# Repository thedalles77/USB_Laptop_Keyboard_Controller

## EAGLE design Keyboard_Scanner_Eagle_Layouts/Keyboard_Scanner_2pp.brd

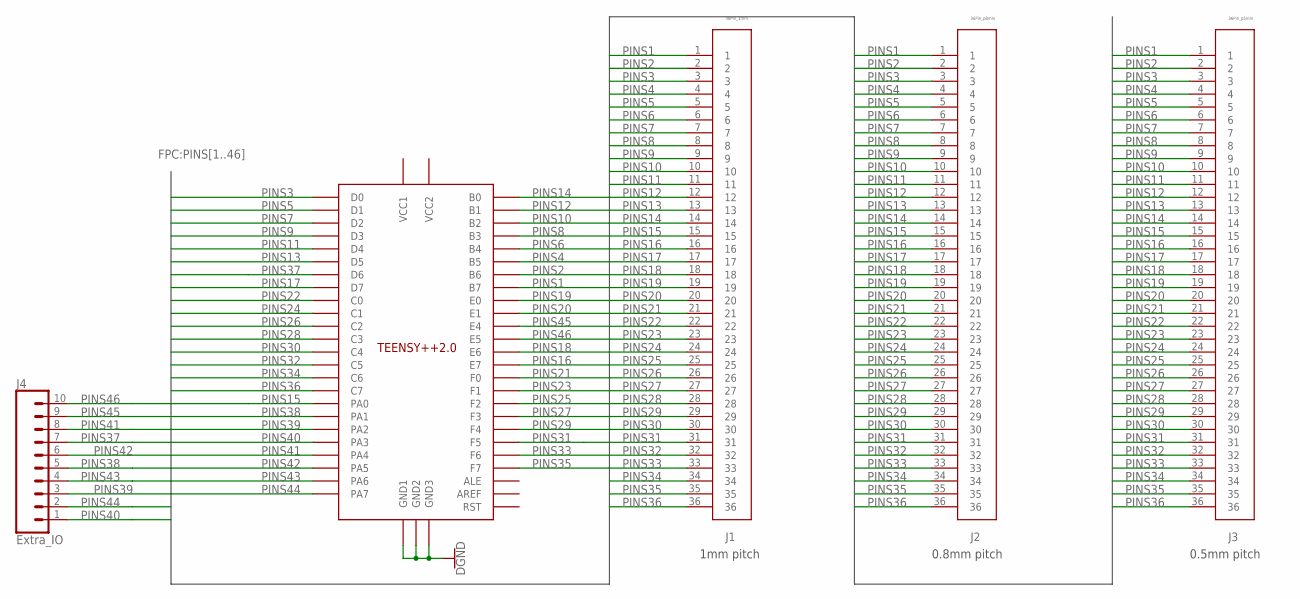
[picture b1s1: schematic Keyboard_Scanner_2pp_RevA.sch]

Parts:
J1: 36Pin_1mm; FPC36_1MM
J2: 36Pin_p8mm; FPC36_P8MM
J3: 36Pin_p5mm; FPC36_P5MM
J4: Extra_IO; 1X10
U$1: Teensy++2.0; TEENSYPP2.0

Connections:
GND: U$1.GND1, U$1.GND2, U$1.GND3
PINS1: J1.1, J2.1, J3.1, U$1.B7
PINS2: J1.2, J2.2, J3.2, U$1.B6
PINS3: J1.3, J2.3, J3.3, U$1.D0
PINS4: J1.4, J2.4, J3.4, U$1.B5
PINS5: J1.5, J2.5, J3.5, U$1.D1
PINS6: J1.6, J2.6, J3.6, U$1.B4
PINS7: J1.7, J2.7, J3.7, U$1.D2
PINS8: J1.8, J2.8, J3.8, U$1.B3
PINS9: J1.9, J2.9, J3.9, U$1.D3
PINS10: J1.10, J2.10, J3.10, U$1.B2
PINS11: J1.11, J2.11, J3.11, U$1.D4
PINS12: J1.12, J2.12, J3.12, U$1.B1
PINS13: J1.13, J2.13, J3.13, U$1.D5
PINS14: J1.14, J2.14, J3.14, U$1.B0
PINS16: J1.16, J2.16, J3.16, U$1.E7
PINS17: J1.17, J2.17, J3.17, U$1.D7
PINS18: J1.18, J2.18, J3.18, U$1.E6
PINS19: J1.19, J2.19, J3.19, U$1.E0
PINS20: J1.20, J2.20, J3.20, U$1.E1
PINS21: J1.21, J2.21, J3.21, U$1.F0
PINS22: J1.22, J2.22, J3.22, U$1.C0
PINS23: J1.23, J2.23, J3.23, U$1.F1
PINS24: J1.24, J2.24, J3.24, U$1.C1
PINS25: J1.25, J2.25, J3.25, U$1.F2
PINS26: J1.26, J2.26, J3.26, U$1.C2
PINS27: J1.27, J2.27, J3.27, U$1.F3
PINS28: J1.28, J2.28, J3.28, U$1.C3
PINS29: J1.29, J2.29, J3.29, U$1.F4
PINS30: J1.30, J2.30, J3.30, U$1.C4
PINS31: J1.31, J2.31, J3.31, U$1.F5
PINS32: J1.32, J2.32, J3.32, U$1.C5
PINS33: J1.33, J2.33, J3.33, U$1.F6
PINS34: J1.34, J2.34, J3.34, U$1.C6
PINS35: J1.35, J2.35, J3.35, U$1.F7
PINS36: J1.36, J2.36, J3.36, U$1.C7
PINS38: J4.5, U$1.PA1
PINS39: J4.3, U$1.PA2
PINS40: J4.1, U$1.PA3
PINS41: J4.8, U$1.PA4
PINS42: J4.6, U$1.PA5
PINS43: J4.4, U$1.PA6
PINS44: J4.2, U$1.PA7
PINS45: J4.9, U$1.E4
PINS46: J4.10, U$1.E5

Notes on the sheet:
1mm pitch
0.8mm pitch
0.5mm pitch

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
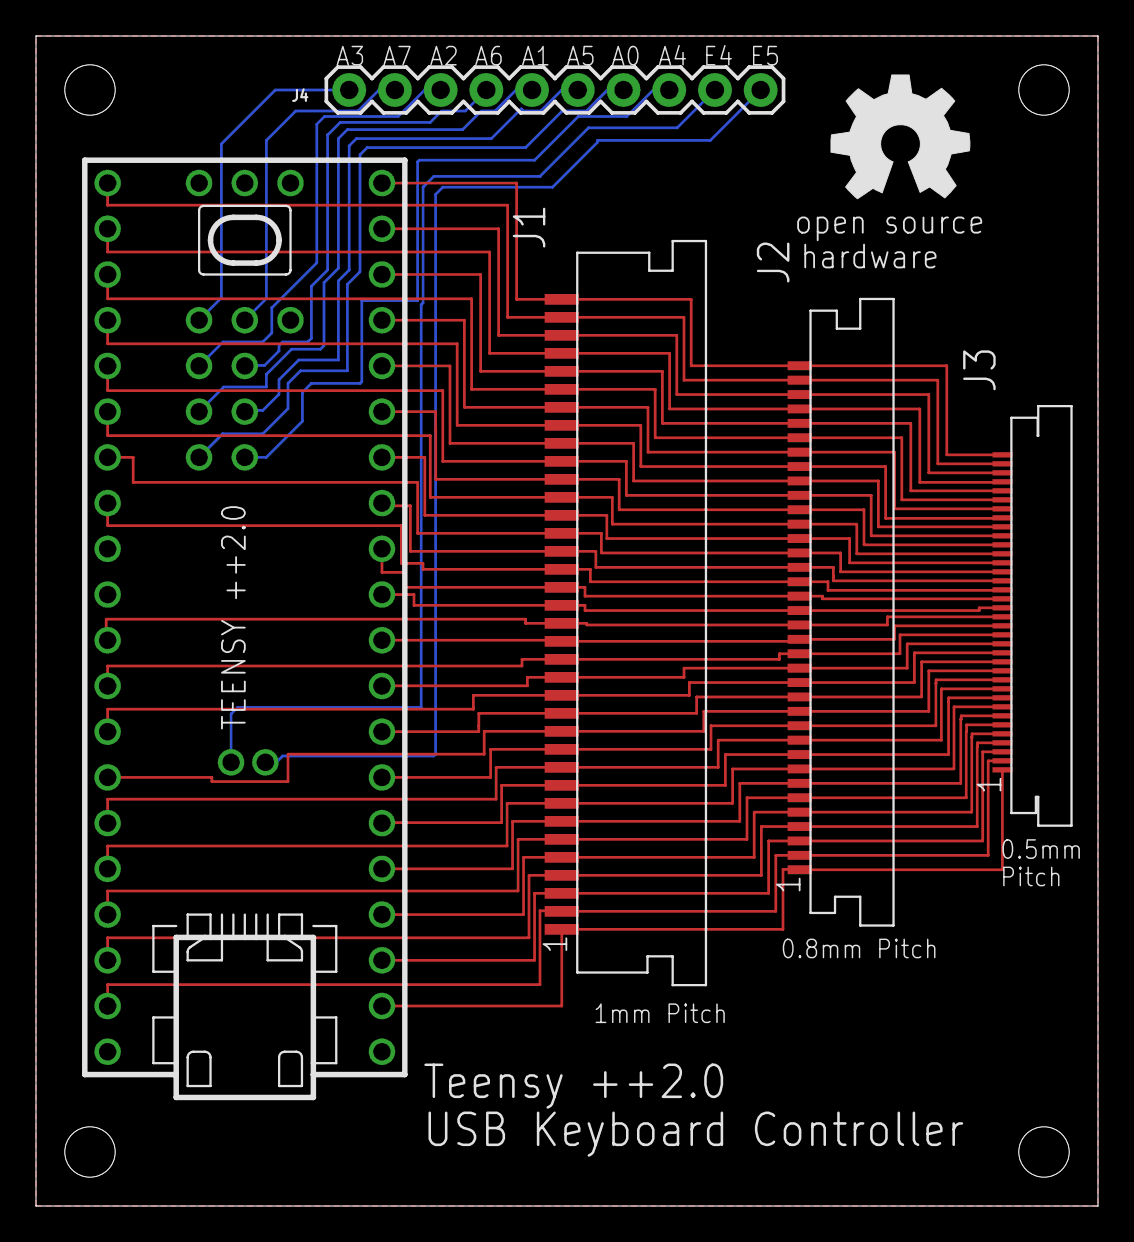
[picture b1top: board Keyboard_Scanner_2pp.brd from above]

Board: 2 copper layers, 59.0 x 65.0 mm, 6 parts (0 on the bottom side), 47 nets.

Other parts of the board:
U$2: OSHW_8MM

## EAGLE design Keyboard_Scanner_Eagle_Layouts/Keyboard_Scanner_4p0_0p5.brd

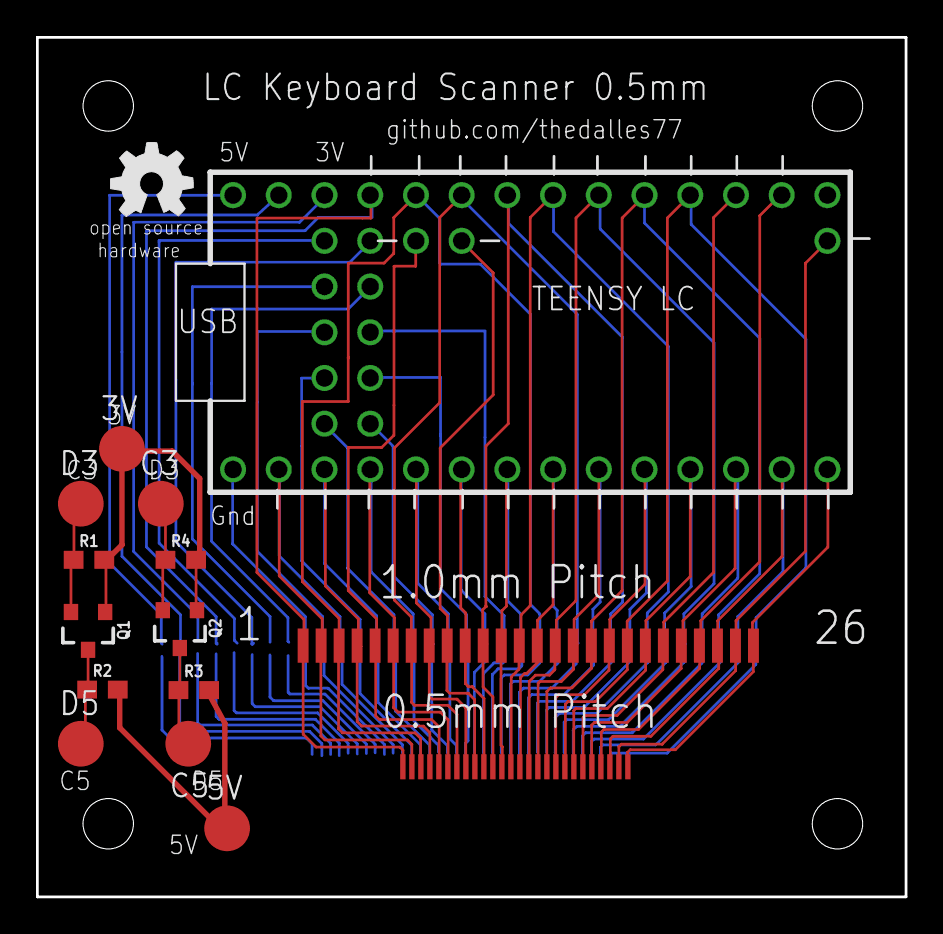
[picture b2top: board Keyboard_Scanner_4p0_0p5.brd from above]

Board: 2 copper layers, 48.3 x 47.8 mm, 16 parts (0 on the bottom side), 4 nets.

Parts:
3V, 5V: B2,54
C3, C5: B2,54
D3, D5: B2,54
E$1: TEENSY_COMBO_4P0
E$2: FPC_DUAL_FRONT_0P5
E$3: FPC_DUAL_BACK_0P5R1
E$4: OSHW_5MM
Q1, Q2: 220mA/50V/3.5Ω; SOT23-3
R1, R2, R3, R4: 10k; 0603

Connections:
CLK: Q1.2, R1.1
DATA: Q2.2, R4.1
TP_CLK: Q1.3, R2.1
TP_DATA: Q2.3, R3.1

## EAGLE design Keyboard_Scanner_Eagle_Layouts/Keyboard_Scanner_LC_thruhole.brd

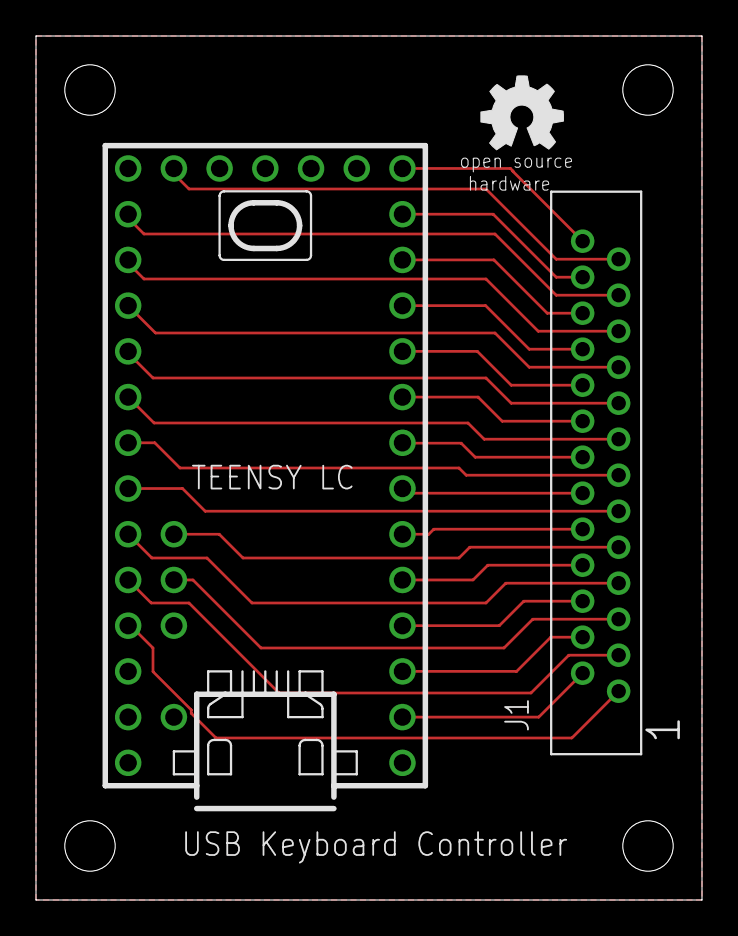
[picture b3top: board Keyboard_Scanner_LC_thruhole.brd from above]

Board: 2 copper layers, 37.0 x 48.0 mm, 3 parts (0 on the bottom side), 27 nets.

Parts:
J1: 1.00MM DIP FPC; T1200_CON
U$1: TEENSY_LC
U$2: OSHW_5MM

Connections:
GND: U$1.GND1, U$1.GND2, U$1.GND3
IO_0: J1.P$2, U$1.0
IO_1: J1.P$4, U$1.1
IO_2: J1.P$6, U$1.2
IO_3: J1.P$8, U$1.3
IO_4: J1.P$10, U$1.4
IO_5: J1.P$12, U$1.5
IO_6: J1.P$14, U$1.6
IO_7: J1.P$16, U$1.7
IO_8: J1.P$18, U$1.8
IO_9: J1.P$20, U$1.9
IO_10: J1.P$22, U$1.10
IO_11: J1.P$24, U$1.11
IO_12: J1.P$26, U$1.12
IO_14: J1.P$23, U$1.14
IO_15: J1.P$21, U$1.15
IO_16: J1.P$19, U$1.16
IO_17: J1.P$17, U$1.17
IO_18: J1.P$15, U$1.18
IO_19: J1.P$13, U$1.19
IO_20: J1.P$11, U$1.20
IO_21: J1.P$7, U$1.21
IO_22: J1.P$3, U$1.22
IO_23: J1.P$1, U$1.23
IO_24: J1.P$5, U$1.24
IO_25: J1.P$9, U$1.25
IO_26: J1.P$25, U$1.26

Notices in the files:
parts and their libraries:
SparkFun-Connectors: Licensing: Creative Commons ShareAlike 4.0 International - https://creativecommons.org/licenses/by-sa/4.0
